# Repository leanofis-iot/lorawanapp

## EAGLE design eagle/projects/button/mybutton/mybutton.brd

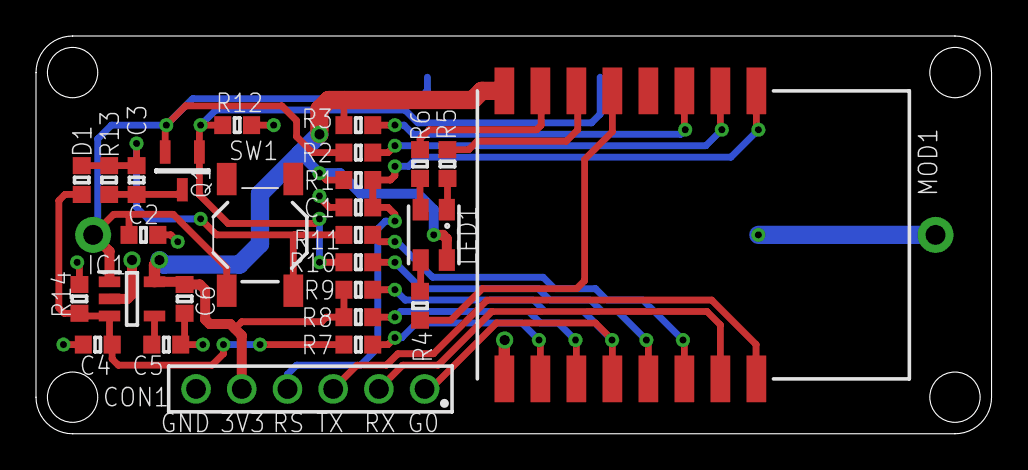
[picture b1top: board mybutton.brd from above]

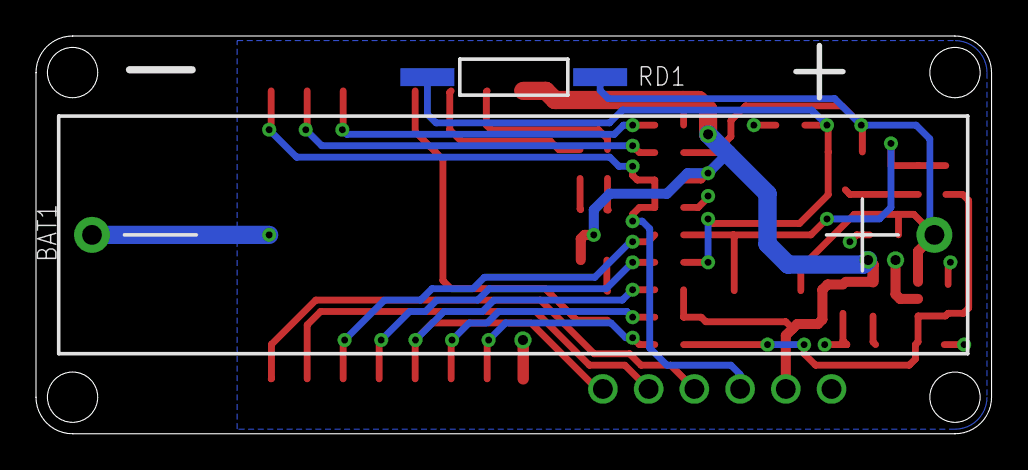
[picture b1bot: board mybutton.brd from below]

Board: 2 copper layers, 53.1 x 22.1 mm, 29 parts (2 on the bottom side), 24 nets.

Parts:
BAT1: BCAAAPC
C1, C2, C3, C4, C5, C6: 0603
CON1: HEADER-6P-DIP-2_54MM
D1: 0603
IC1: SOT23-5
LED1: LED-RGB-3528-PLCC4
MOD1: ESP-12S
Q1: SOT23-3
R1, R2, R3, R4, R5, R6, R7, R8, R9, R10, R11, R12, R13, R14: 0603
RD1: REED-SMD-5MM
SW1: BUTTON-4P-SMD-5X5

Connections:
GND: BAT1.2, C1.1, C2.1, C4.1, C5.1, C6.1, CON1.6, IC1.2, MOD1.9, R12.1, R14.1
unnamed: CON1.1, MOD1.12, R9.2
unnamed: CON1.2, MOD1.15
unnamed: CON1.3, MOD1.16
unnamed: C1.2, CON1.4, MOD1.1, R1.2
unnamed: MOD1.2, R2.2
unnamed: MOD1.3, R3.2
unnamed: MOD1.5, R4.2
unnamed: MOD1.6, R5.2
unnamed: MOD1.7, R6.2
unnamed: LED1.1, R5.1
unnamed: LED1.2, R6.1
unnamed: LED1.3, R4.1
unnamed: BAT1.1, C2.2, IC1.1, Q1.2, R2.1, RD1.P$2, SW1.1
unnamed: MOD1.14, R11.1
unnamed: MOD1.13, R10.1
unnamed: Q1.1, R10.2, R12.2, RD1.P$1
unnamed: MOD1.11, R8.1
unnamed: C3.1, Q1.3, R13.1
unnamed: C3.2, D1.1, R11.2, R13.2, SW1.2
unnamed: C5.2, IC1.4
unnamed: C4.2, D1.2, IC1.3, R7.2, R14.2
unnamed: MOD1.10, R7.1
VCC: C6.2, CON1.5, IC1.5, LED1.4, MOD1.8, R1.1, R3.1, R8.2, R9.1

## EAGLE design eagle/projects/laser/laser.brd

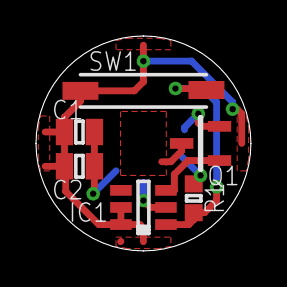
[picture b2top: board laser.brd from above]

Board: 2 copper layers, 11.9 x 11.9 mm, 6 parts (0 on the bottom side), 4 nets.

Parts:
C1, C2: 0805
IC1: SOT23-6
Q1: SOT23-3
R1: 0603
SW1: REED-7MM-SMD

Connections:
GND: C1.1, C2.1, IC1.2, Q1.2, R1.1
unnamed: IC1.3, Q1.1
unnamed: IC1.1, R1.2, SW1.P$2
VCC: C1.2, C2.2, IC1.5, IC1.6, SW1.P$1

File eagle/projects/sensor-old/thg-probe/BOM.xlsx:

IC1 | SHT31-DIS | DFN-8
IC2 | CCS811 | LGA-10
CON1 | HEADER 2.54MM 10P 2R | DIP
C1 | 100NF | 0603
C2 | 4.7UF | 0603
PCB
SHELL WATERPROOF

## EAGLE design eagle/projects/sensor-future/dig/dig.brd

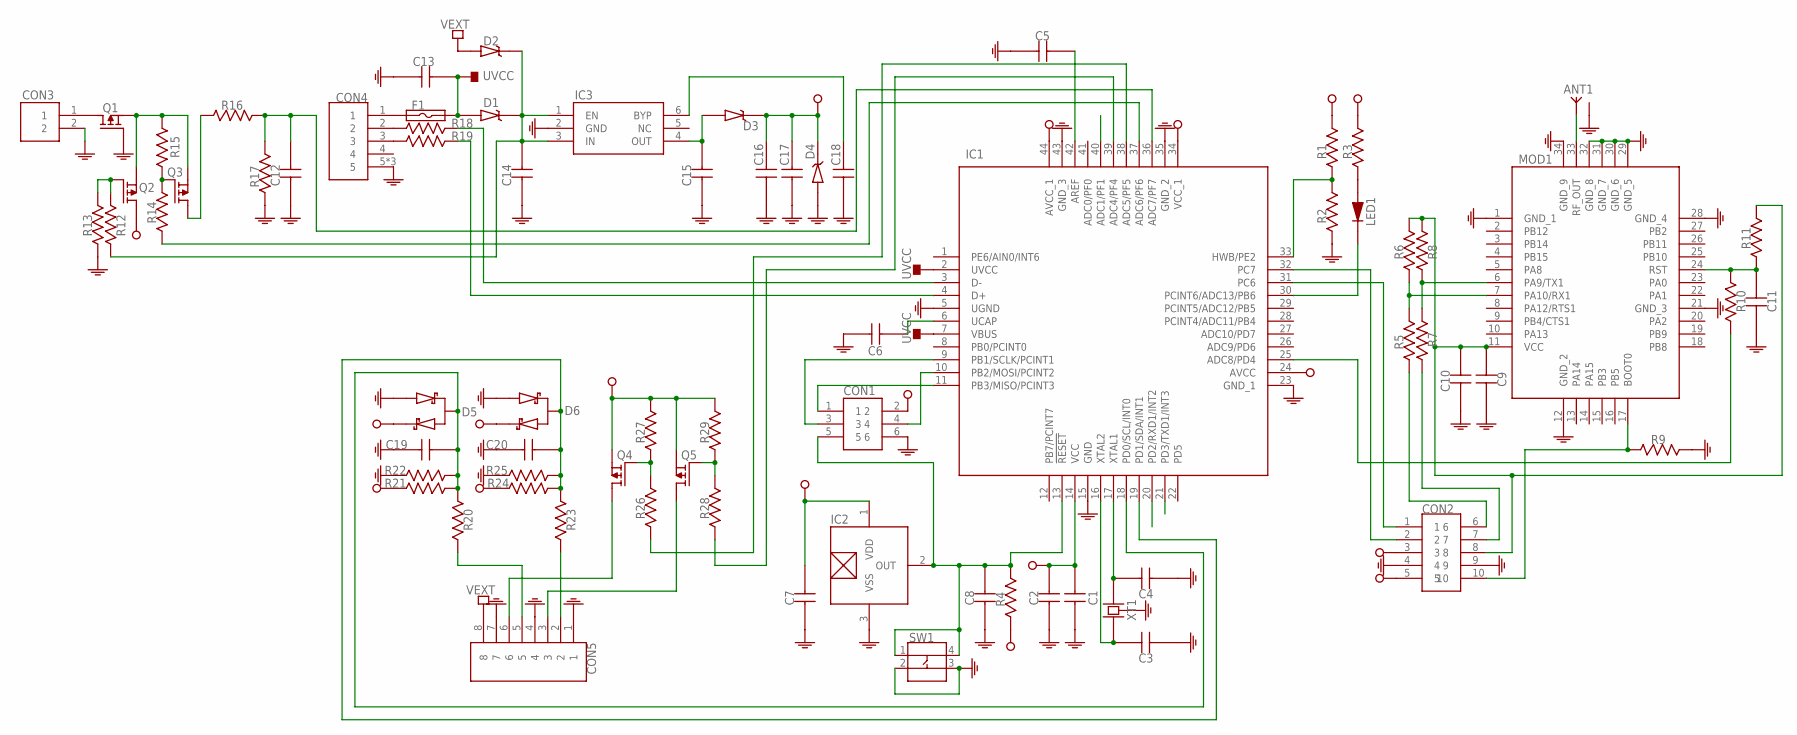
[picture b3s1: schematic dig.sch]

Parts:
ANT1: SMA-RF
C1, C2, C3, C4, C5, C6, C7, C8, C9, C10, C11, C12, C13, C16, C17, C18, C19, C20: CAPACITOR-0603; 0603
C14, C15: CAPACITOR-0805; 0805
CON1: ISP
CON2: HEADER-10P-2R-DIP-2_54MM
CON3: JST-PH-2-2.0MM
CON4: USB-MICRO-DIP-VER
CON5: CON-3_50MM-8P-1985250
D1, D2, D3: DIODE-SCHOTTKY; SOD123-DIODE
D4: ZENER-SOD123; SOD123-DIODE
D5, D6: SCHOTTKY-SERIE-3P; SOT23-3
F1: FUSE-0805; 0805
IC1: ATMEGA32U4-MU; QFN-44
IC2: S-5712-SOT23-3; SOT23-3
IC3: MIC5219-VDFN-6; VDFN-6
LED1: LED-0603
MOD1: RAK811
Q1, Q2, Q3, Q4, Q5: P-MOSFET; SOT23-3
R1, R2, R3, R4, R5, R6, R7, R8, R9, R10, R11, R12, R13, R14, R15, R16, R17, R18, R19, R26, R27, R28, R29: RESISTOR-0603; 0603
R20, R21, R22, R23, R24, R25: RESISTOR-JMP-2_54MM; HEADER-2P-DIP-2_54MM
SW1: BUTTON-4P-SMD-5X5
XT1: CRYSTAL-5032-4P

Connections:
GND: ANT1.2 (GND), ANT1.3 (GND), ANT1.4 (GND), ANT1.5 (GND), C1.1, C2.1, C3.1, C4.1, C5.1, C6.1, C7.1, C8.1, C9.1, C10.1, C11.1, C12.1, C13.1, C14.1, C15.1, C16.1, C17.1, C18.1, C19.2, C20.2, CON1.6, CON2.4, CON2.9, CON3.2, CON4.5, CON4.6 (5), CON4.7 (5), CON5.1, CON5.4, CON5.7, D4.2 (A), D5.1, D6.1, IC1.5 (UGND), IC1.15 (GND), IC1.23 (GND_1), IC1.35 (GND_2), IC1.43 (GND_3), IC2.3 (VSS), IC3.2 (GND), MOD1.1 (GND_1), MOD1.12 (GND_2), MOD1.21 (GND_3), MOD1.28 (GND_4), MOD1.29 (GND_5), MOD1.30 (GND_6), MOD1.31 (GND_7), MOD1.32 (GND_8), MOD1.34 (GND_9), Q1.1 (G), R2.1, R9.2, R13.1, R17.1, R22.2, R25.2, SW1.2, SW1.3, XT1.2 (GND), XT1.4 (GND)
unnamed: CON5.6, Q4.3 (D)
unnamed: C11.2, MOD1.24 (RST), R10.1, R11.1
unnamed: CON1.1, IC1.11 (PB3/MISO/PCINT3)
unnamed: ANT1.1 (ANT), MOD1.33 (RF_OUT)
unnamed: C19.1, D5.3, IC1.18 (PD0/SCL/INT0), R20.1, R21.1, R22.1
unnamed: MOD1.7 (PA10/RX1), R5.2, R6.1
unnamed: MOD1.6 (PA9/TX1), R7.2, R8.1
unnamed: CON5.3, Q5.3 (D)
unnamed: CON1.4, IC1.10 (PB2/MOSI/PCINT2)
unnamed: C3.2, IC1.16 (XTAL2), XT1.1
unnamed: CON2.1, IC1.31 (PC6)
unnamed: C4.2, IC1.17 (XTAL1), XT1.3 (2)
unnamed: C9.2, C10.2, CON2.8, MOD1.11 (VCC), R6.2, R8.2, R11.2
unnamed: CON2.7, R7.1
unnamed: C20.1, D6.3, IC1.19 (PD1/SDA/INT1), R23.1, R24.1, R25.1
unnamed: IC1.25 (ADC8/PD4), R10.2
unnamed: IC1.30 (PCINT6/ADC13/PB6), LED1.1 (K)
unnamed: CON5.2, R23.2
unnamed: CON5.5, R20.2
unnamed: Q5.1 (G), R28.2, R29.1
unnamed: CON2.2, IC1.32 (PC7)
unnamed: C5.2, IC1.42 (AREF)
unnamed: Q3.1 (G), R14.2, R15.2
unnamed: CON4.1, F1.1
unnamed: C6.2, IC1.6 (UCAP)
unnamed: LED1.2 (A), R3.1
unnamed: C12.2, IC1.36 (ADC7/PF7), R16.2, R17.2
unnamed: C18.2, IC3.6 (BYP)
unnamed: C14.2, D1.1 (K), D2.1 (K), IC3.1 (EN), IC3.3 (IN), R12.1
unnamed: C15.2, D3.2 (A), IC3.4 (OUT)
unnamed: CON4.2, R18.1
unnamed: CON4.3, R19.1
unnamed: IC1.3 (D-), R18.2
unnamed: IC1.4 (D+), R19.2
unnamed: CON1.3, IC1.9 (PB1/SCLK/PCINT1)
unnamed: Q4.1 (G), R26.2, R27.1
unnamed: IC1.37 (ADC6/PF6), R14.1
unnamed: IC1.38 (ADC5/PF5), R26.1
unnamed: IC1.39 (ADC4/PF4), R28.1
unnamed: Q2.1 (G), R12.2, R13.2
unnamed: CON3.1, Q1.3 (D)
unnamed: Q1.2 (S), Q2.2 (S), Q3.2 (S), R15.1
unnamed: Q3.3 (D), R16.1
unnamed: CON2.6, R5.1
unnamed: IC1.33 (HWB/PE2), R1.1, R2.2
unnamed: CON2.10, MOD1.17 (BOOT0), R9.1
unnamed: C8.2, CON1.5, IC1.13 (!RESET), IC2.2 (OUT), R4.2, SW1.1, SW1.4
UVCC: C13.2, D1.2 (A), F1.2, IC1.2 (UVCC), IC1.7 (VBUS)
VCC: C1.2, C2.2, C7.2, C16.2, C17.2, CON1.2, CON2.3, CON2.5, D3.1 (K), D4.1 (K), D5.2, D6.2, IC1.14 (VCC), IC1.24 (AVCC), IC1.34 (VCC_1), IC1.44 (AVCC_1), IC2.1 (VDD), Q2.3 (D), Q4.2 (S), Q5.2 (S), R1.2, R3.2, R4.1, R21.2, R24.2, R27.2, R29.2
VEXT: CON5.8, D2.2 (A)

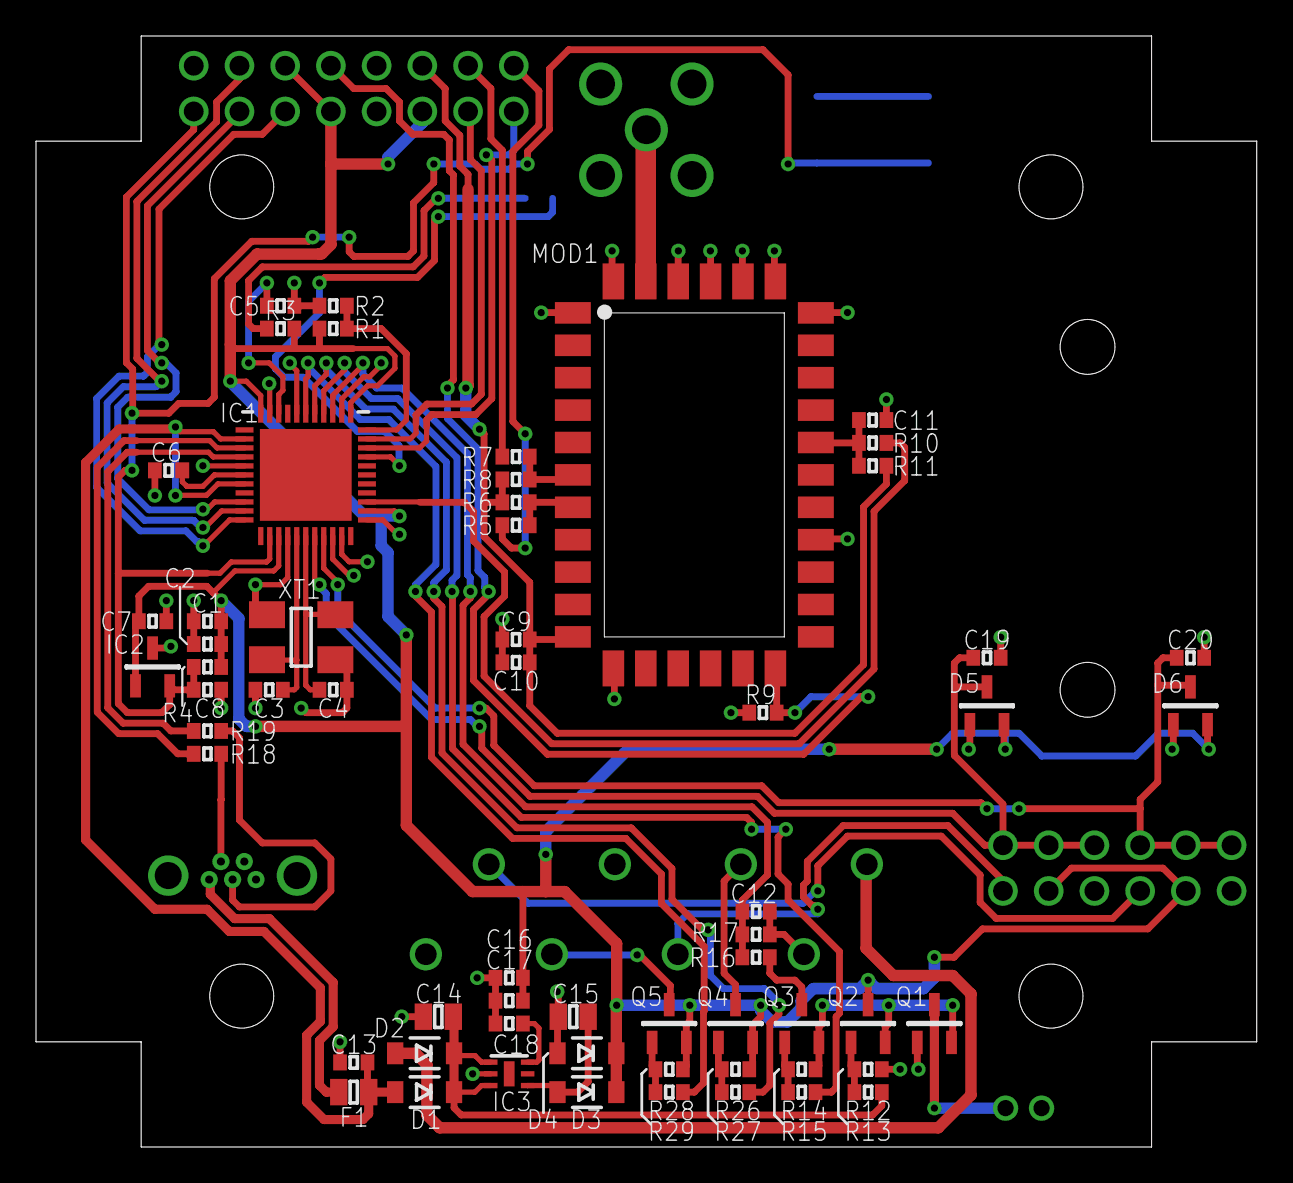
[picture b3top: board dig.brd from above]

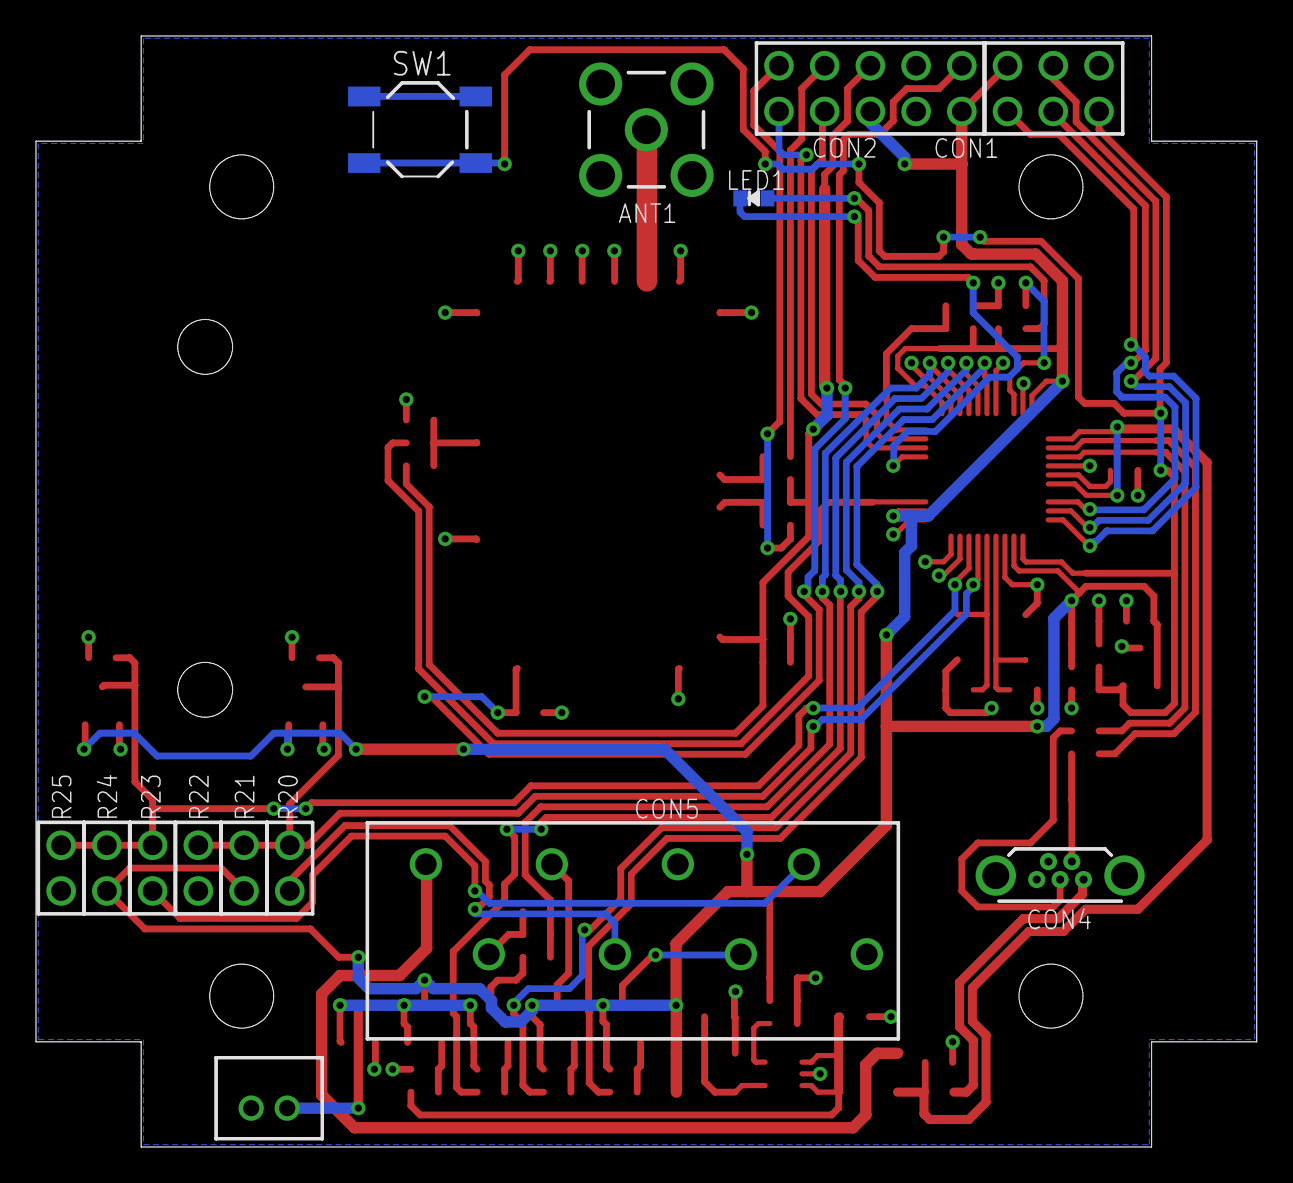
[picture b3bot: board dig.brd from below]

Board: 2 copper layers, 67.8 x 61.7 mm, 74 parts (14 on the bottom side), 51 nets.

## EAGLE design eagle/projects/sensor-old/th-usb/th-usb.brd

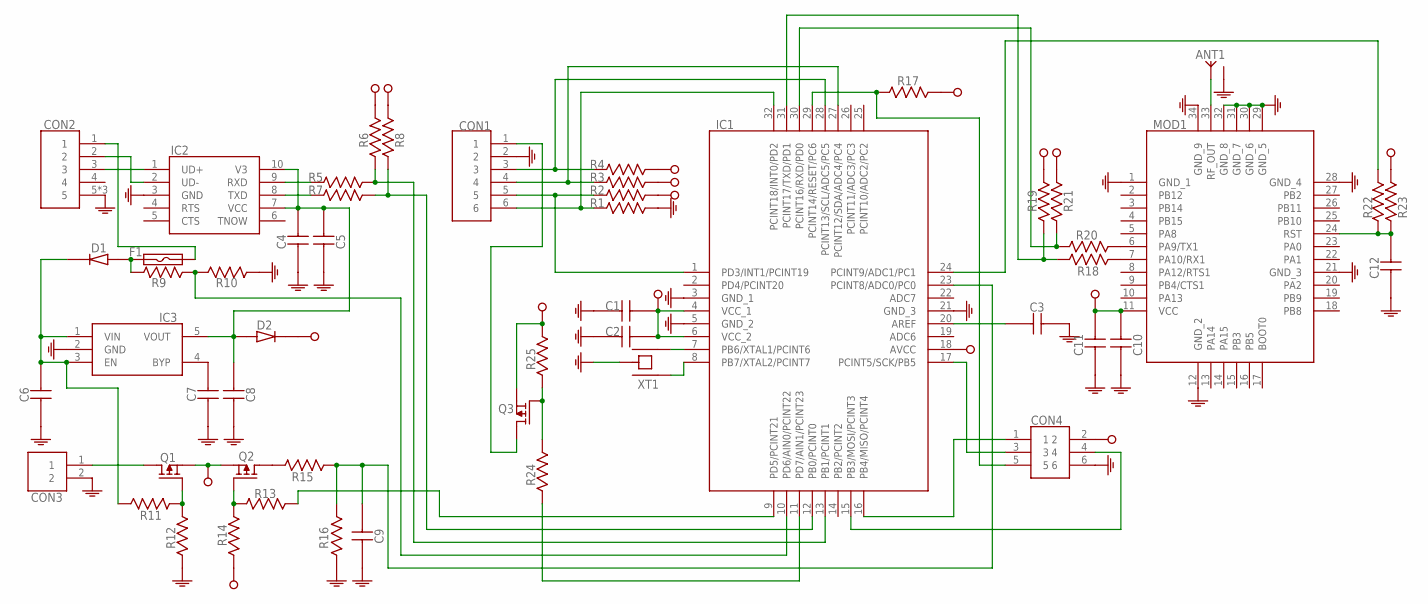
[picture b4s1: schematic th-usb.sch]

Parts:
ANT1: SMA-RF
C1, C4, C6, C8, C10: CAPACITOR-0805; 0805
C2, C3, C5, C7, C9, C11, C12: CAPACITOR-0603; 0603
CON1: CON-6P-3_81-PLUG
CON2: USB-MICRO-DIP-VER
CON3: JST-PH-2-2.0MM
CON4: ISP
D1, D2: DIODE-SOD123; SOD123-DIODE
F1: FUSE-0805; 0805
IC1: ATMEGA328P-AU; TQFP-32
IC2: CH340E; MSOP-10
IC3: MIC5219; SOT23-5
MOD1: RAK811
Q1, Q2, Q3: P-MOSFET; SOT23-3
R1, R2, R3, R4, R5, R6, R7, R8, R9, R10, R11, R12, R13, R14, R15, R16, R17, R18, R19, R20, R21, R22, R23, R24, R25: RESISTOR-0603; 0603
XT1: RESONATOR-3215

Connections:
GND: ANT1.2 (GND), ANT1.3 (GND), ANT1.4 (GND), ANT1.5 (GND), C1.1, C2.1, C3.2, C4.1, C5.1, C6.1, C7.2, C8.1, C9.1, C10.1, C11.1, C12.1, CON1.2, CON2.5, CON2.6 (5), CON2.7 (5), CON3.2, CON4.6, IC1.3 (GND_1), IC1.5 (GND_2), IC1.21 (GND_3), IC2.3 (GND), IC3.2 (GND), MOD1.1 (GND_1), MOD1.12 (GND_2), MOD1.21 (GND_3), MOD1.28 (GND_4), MOD1.29 (GND_5), MOD1.30 (GND_6), MOD1.31 (GND_7), MOD1.32 (GND_8), MOD1.34 (GND_9), R1.2, R10.1, R12.1, R16.1, XT1.3
unnamed: D1.2 (A), F1.2, R9.1
unnamed: C7.1, IC3.4 (BYP)
unnamed: IC2.9 (RXD), R5.1
unnamed: IC2.8 (TXD), R7.1
unnamed: CON2.3, IC2.1 (UD+)
unnamed: CON2.2, IC2.2 (UD-)
unnamed: CON3.1, Q1.3 (D)
unnamed: IC1.7 (PB6/XTAL1/PCINT6), XT1.1
unnamed: CON2.1, F1.1
unnamed: IC1.8 (PB7/XTAL2/PCINT7), XT1.2
unnamed: IC1.9 (PD5/PCINT21), R13.2
unnamed: C6.2, D1.1 (K), IC3.1 (VIN), IC3.3 (EN), R11.2
unnamed: Q2.1 (G), R13.1, R14.2
unnamed: Q2.3 (D), R15.1
unnamed: CON1.6, IC1.32 (PCINT18/INT0/PD2), R1.1
unnamed: ANT1.1 (ANT), MOD1.33 (RF_OUT)
unnamed: MOD1.6 (PA9/TX1), R20.2
unnamed: MOD1.7 (PA10/RX1), R18.2
unnamed: C12.2, MOD1.24 (RST), R22.1, R23.1
unnamed: IC1.30 (PCINT16/RXD/PD0), R20.1, R21.1
unnamed: IC1.31 (PCINT17/TXD/PD1), R18.1, R19.1
unnamed: CON4.5, IC1.29 (PCINT14/RESET/PC6), R17.1
unnamed: IC1.13 (PB1/PCINT1), R5.2, R6.1
unnamed: CON1.4, IC1.27 (PCINT12/SDA/ADC4/PC4), R3.1
unnamed: IC1.12 (PB0/PCINT0), R7.2, R8.1
unnamed: CON1.5, IC1.1 (PD3/INT1/PCINT19), R2.1
unnamed: CON1.3, IC1.28 (PCINT13/SCL/ADC5/PC5), R4.1
unnamed: C3.1, IC1.20 (AREF)
unnamed: C9.2, IC1.23 (PCINT8/ADC0/PC0), R15.2, R16.2
unnamed: Q3.1 (G), R24.2, R25.1
unnamed: CON1.1, Q3.3 (D)
unnamed: IC1.11 (PD7/AIN1/PCINT23), R24.1
unnamed: C4.2, C5.2, C8.2, D2.2 (A), IC2.7 (VCC), IC2.10 (V3), IC3.5 (VOUT)
unnamed: IC1.24 (PCINT9/ADC1/PC1), R22.2
unnamed: Q1.1 (G), R11.1, R12.2
unnamed: IC1.10 (PD6/AIN0/PCINT22), R9.2, R10.2
unnamed: CON4.3, IC1.17 (PCINT5/SCK/PB5)
unnamed: CON4.1, IC1.16 (PB4/MISO/PCINT4)
unnamed: CON4.4, IC1.15 (PB3/MOSI/PCINT3)
PD4/PCINT20: IC1.2 (PD4/PCINT20)
VCC: C1.2, C2.2, C10.2, C11.2, CON4.2, D2.1 (K), IC1.4 (VCC_1), IC1.6 (VCC_2), IC1.18 (AVCC), MOD1.11 (VCC), Q1.2 (S), Q2.2 (S), Q3.2 (S), R2.2, R3.2, R4.2, R6.2, R8.2, R14.1, R17.2, R19.2, R21.2, R23.2, R25.2

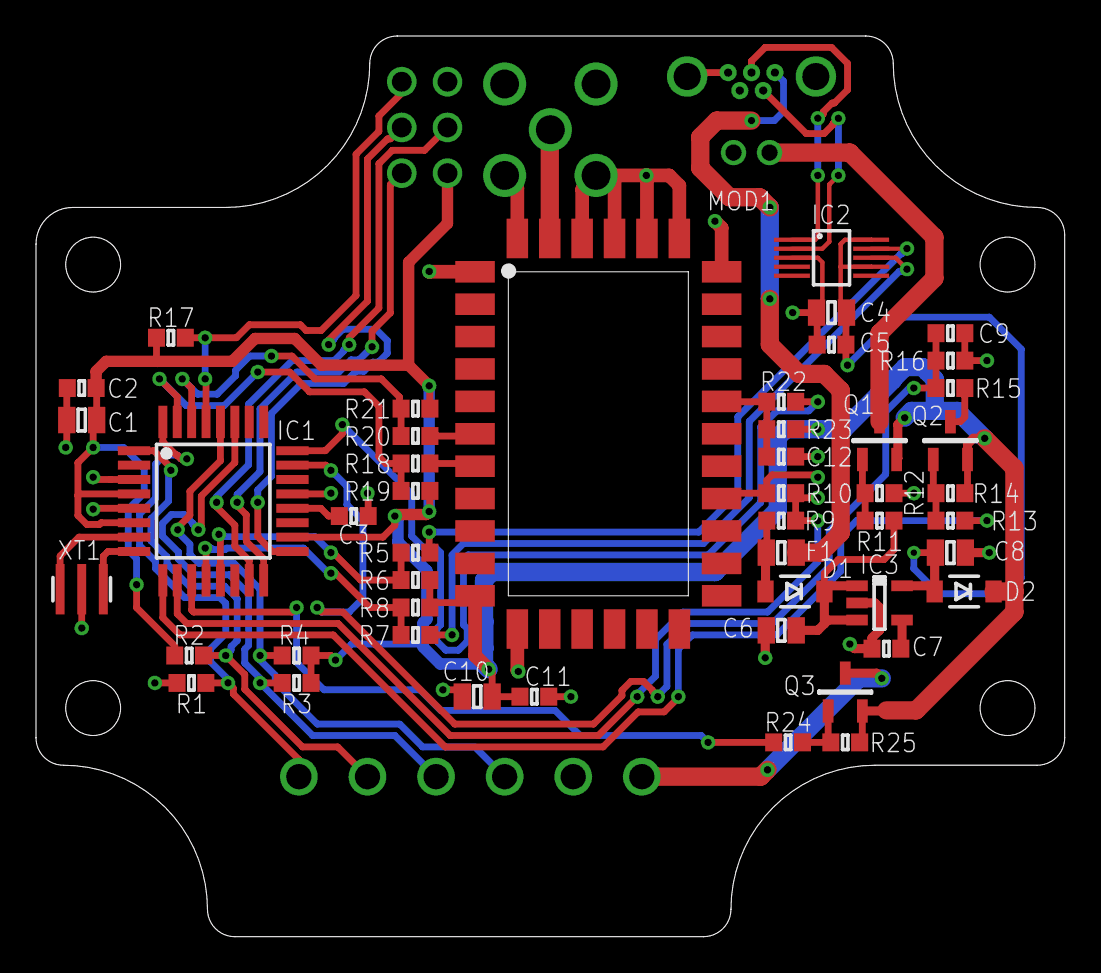
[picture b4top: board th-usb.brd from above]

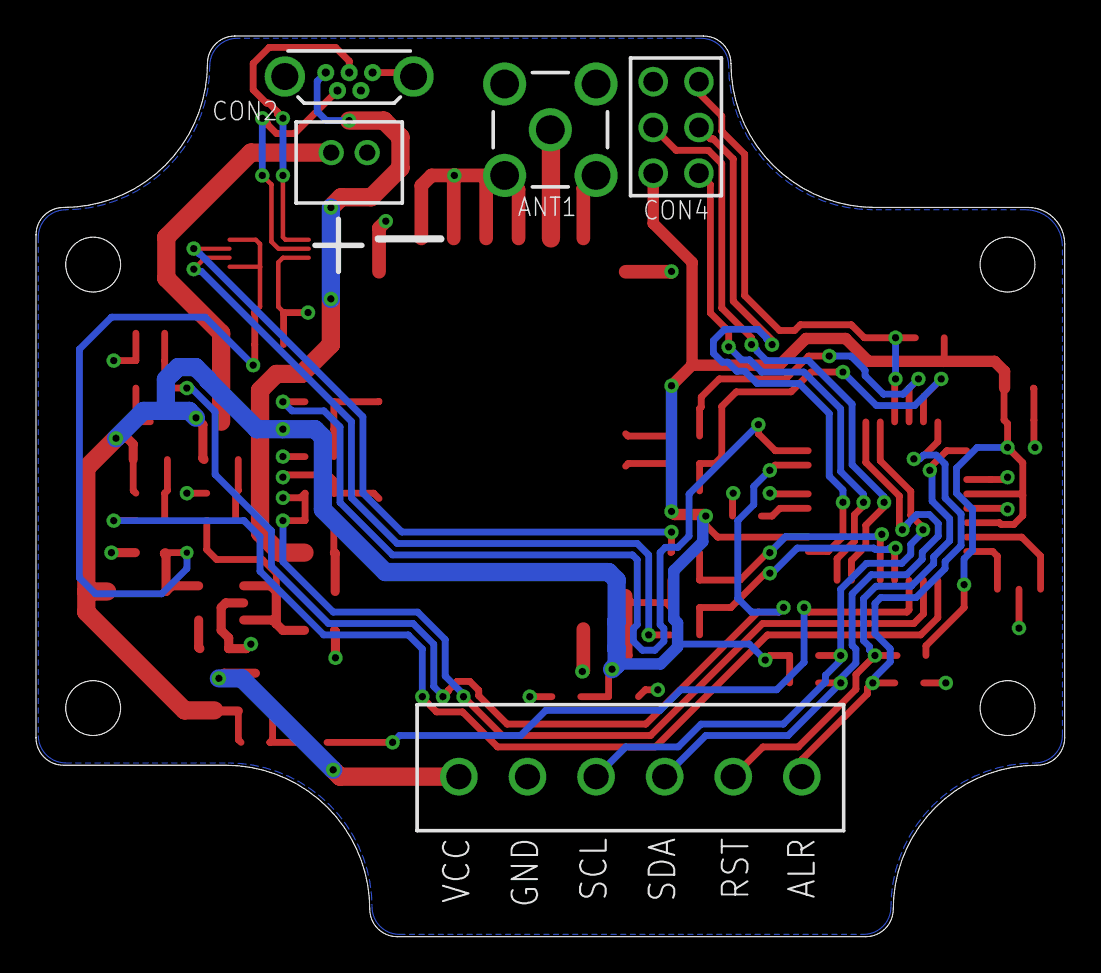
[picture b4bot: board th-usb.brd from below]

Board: 2 copper layers, 57.1 x 50.0 mm, 53 parts (5 on the bottom side), 41 nets.

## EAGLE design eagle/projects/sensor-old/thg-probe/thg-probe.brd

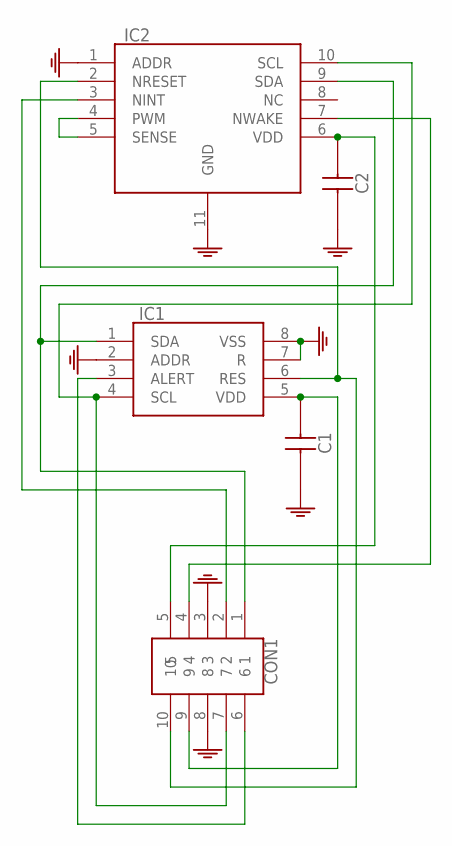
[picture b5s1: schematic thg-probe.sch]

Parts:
C1, C2: CAPACITOR-0603; 0603
CON1: HEADER-10P-2R-DIP-2_54MM
IC1: SHT3X-DIS
IC2: CCS811B-JOPD500; LGA-10

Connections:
GND: C1.2, C2.2, CON1.3, CON1.8, IC1.2 (ADDR), IC1.7 (R), IC1.8 (VSS), IC2.1 (ADDR), IC2.11 (GND)
unnamed: CON1.10, IC1.6 (RES), IC2.2 (NRESET)
unnamed: C1.1, CON1.9, IC1.5 (VDD)
unnamed: C2.1, CON1.5, IC2.6 (VDD)
unnamed: CON1.4, IC2.7 (NWAKE)
unnamed: CON1.1, IC1.1 (SDA), IC2.9 (SDA)
unnamed: IC2.4 (PWM), IC2.5 (SENSE)
unnamed: CON1.2, IC2.3 (NINT)
unnamed: CON1.7, IC1.4 (SCL), IC2.10 (SCL)
unnamed: CON1.6, IC1.3 (ALERT)

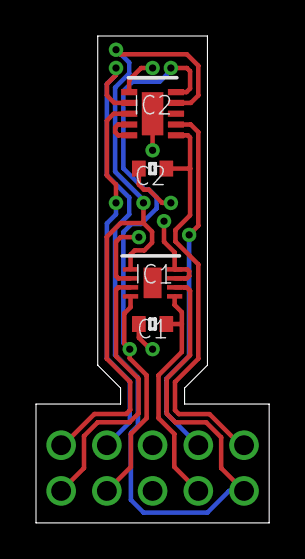
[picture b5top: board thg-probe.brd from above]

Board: 2 copper layers, 13.0 x 27.1 mm, 5 parts (1 on the bottom side), 10 nets.
